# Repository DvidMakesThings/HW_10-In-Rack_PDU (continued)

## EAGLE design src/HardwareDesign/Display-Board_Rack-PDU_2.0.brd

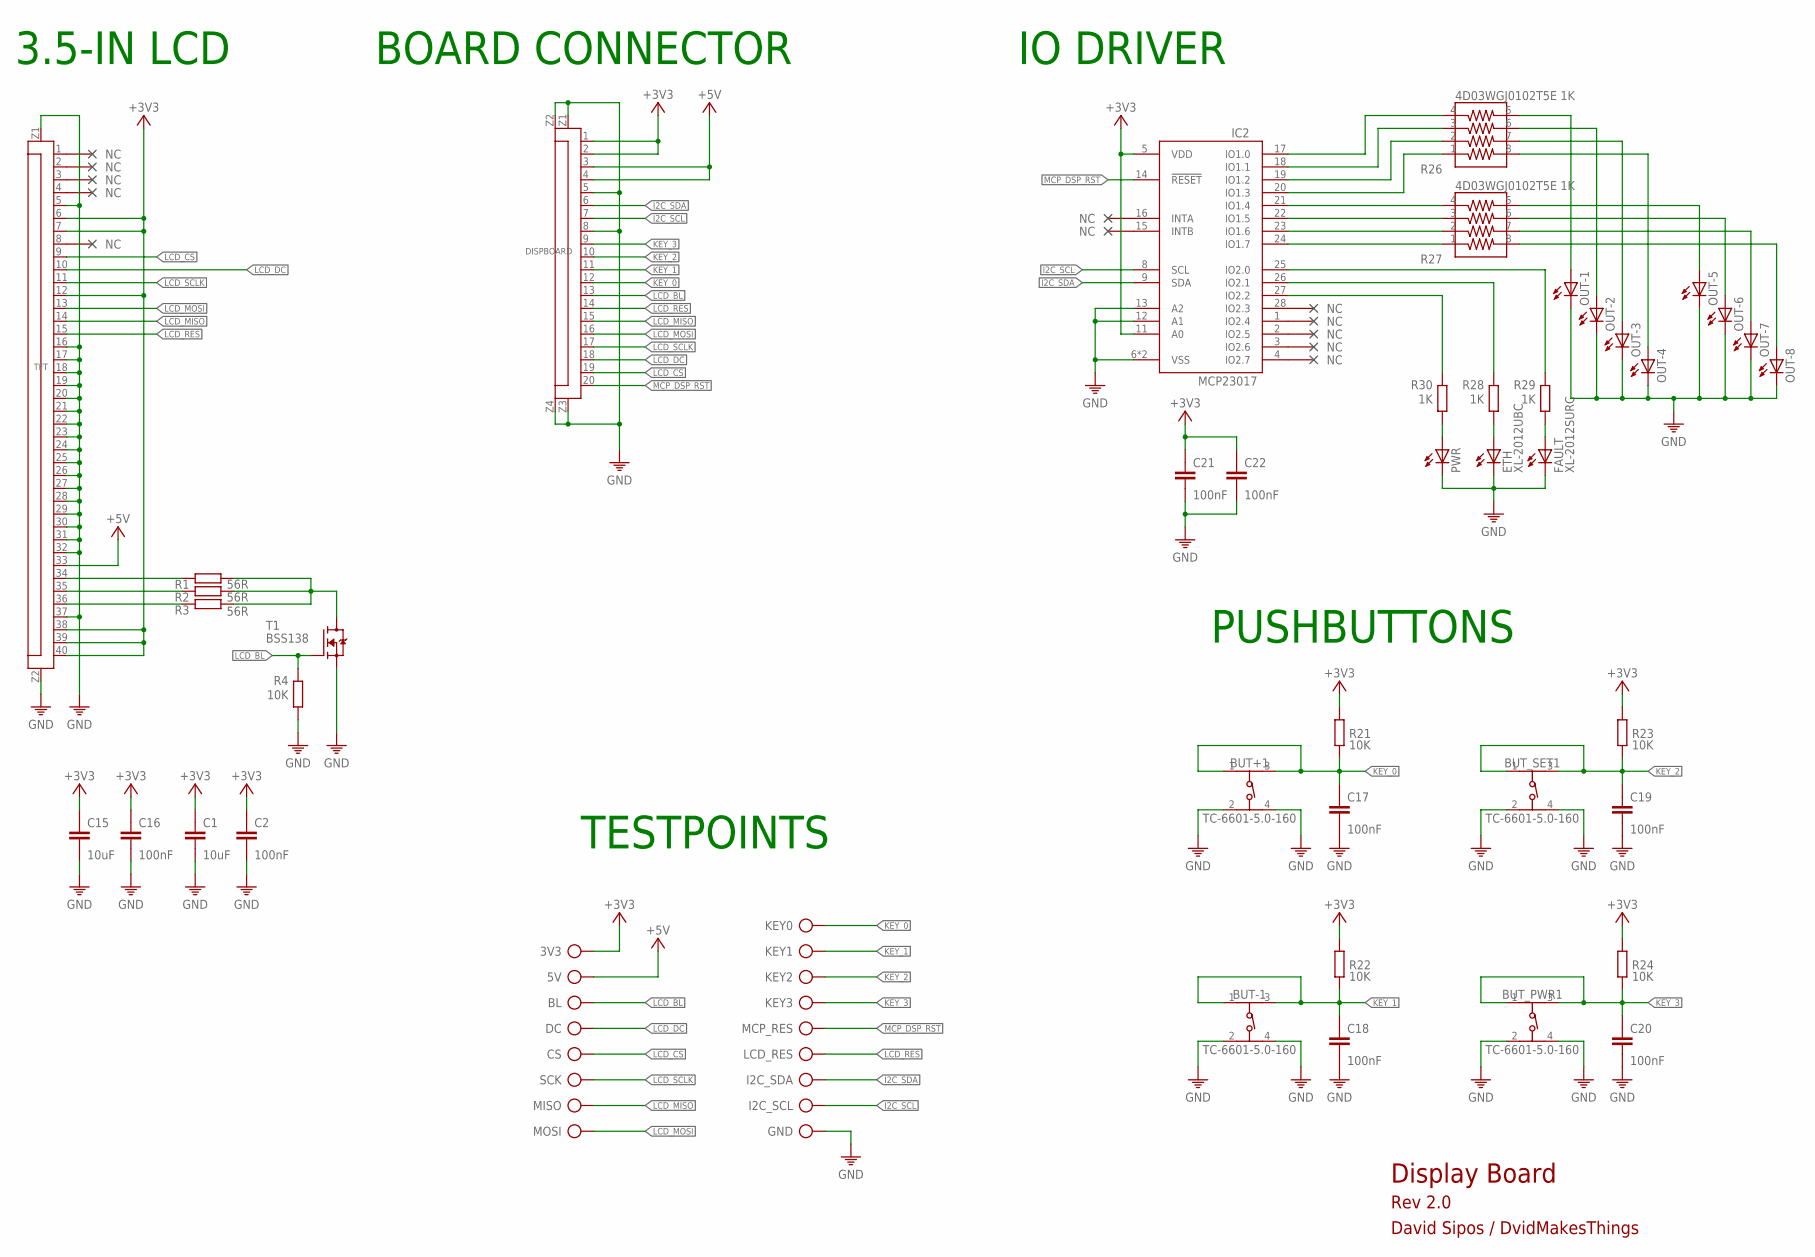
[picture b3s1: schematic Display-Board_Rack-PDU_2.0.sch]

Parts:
3V3, 5V: TP
BL: TP
BUT+1: TC-6601-5.0-160; 430182043816
BUT-1: TC-6601-5.0-160; 430182043816
BUT_PWR1: TC-6601-5.0-160; 430182043816
BUT_SET1: TC-6601-5.0-160; 430182043816
C1, C15: 10uF; C0402
C2, C16, C17, C18, C19, C20, C21, C22: 100nF; C0402
CS: TP
DC: TP
DISPBOARD: FPC20-H; FPC20
ETH: XL-2012UBC; CHIP-LED0805
FAULT: XL-2012SURC; CHIP-LED0805
GND: TP
I2C_SCL, I2C_SDA: TP
IC2: MCP23017-E/ML; QFN28[6X6]ML
KEY0, KEY1, KEY2, KEY3: TP
LCD_RES: TP
MCP_RES: TP
MISO: TP
MOSI: TP
OUT-1, OUT-2, OUT-3, OUT-4, OUT-5, OUT-6, OUT-7, OUT-8: LEDCHIP-LED0805; CHIP-LED0805
PWR: LEDCHIP-LED0805; CHIP-LED0805
R1, R2, R3: 56R; 0402
R4, R21, R22, R23, R24: 10K; 0402
R26, R27: 4D03WGJ0102T5E 1K; 742C083103JP
R28, R29, R30: 1K; 0402
SCK: TP
T1: BSS138; SOT23
TFT: FPC40-HD; FPC40_3.5TFT

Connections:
+3V3: 3V3.TP, C1.1, C2.1, C15.1, C16.1, C21.1, C22.1, DISPBOARD.1, DISPBOARD.2, IC2.5 (VDD), IC2.11 (A0), R21.1, R22.1, R23.1, R24.1, TFT.6, TFT.7, TFT.12, TFT.38, TFT.39, TFT.40
+5V: 5V.TP, DISPBOARD.3, DISPBOARD.4, TFT.33
GND: BUT+1.2, BUT+1.4, BUT-1.2, BUT-1.4, BUT_PWR1.2, BUT_PWR1.4, BUT_SET1.2, BUT_SET1.4, C1.2, C2.2, C15.2, C16.2, C17.2, C18.2, C19.2, C20.2, C21.2, C22.2, DISPBOARD.5, DISPBOARD.8, DISPBOARD.Z1, DISPBOARD.Z2, DISPBOARD.Z3, DISPBOARD.Z4, ETH.C, FAULT.C, GND.TP, IC2.6 (VSS), IC2.12 (A1), IC2.13 (A2), IC2.PAD (VSS), OUT-1.C, OUT-2.C, OUT-3.C, OUT-4.C, OUT-5.C, OUT-6.C, OUT-7.C, OUT-8.C, PWR.C, R4.2, T1.2 (S), TFT.5, TFT.16, TFT.17, TFT.18, TFT.19, TFT.20, TFT.21, TFT.22, TFT.23, TFT.24, TFT.25, TFT.26, TFT.27, TFT.28, TFT.29, TFT.30, TFT.31, TFT.32, TFT.37, TFT.Z1, TFT.Z2
I2C_SCL: DISPBOARD.7, I2C_SCL.TP, IC2.8 (SCL)
I2C_SDA: DISPBOARD.6, I2C_SDA.TP, IC2.9 (SDA)
KEY_0: BUT+1.1, BUT+1.3, C17.1, DISPBOARD.12, KEY0.TP, R21.2
KEY_1: BUT-1.1, BUT-1.3, C18.1, DISPBOARD.11, KEY1.TP, R22.2
KEY_2: BUT_SET1.1, BUT_SET1.3, C19.1, DISPBOARD.10, KEY2.TP, R23.2
KEY_3: BUT_PWR1.1, BUT_PWR1.3, C20.1, DISPBOARD.9, KEY3.TP, R24.2
LCD_BL: BL.TP, DISPBOARD.13, R4.1, T1.1 (G)
LCD_CS: CS.TP, DISPBOARD.19, TFT.9
LCD_DC: DC.TP, DISPBOARD.18, TFT.10
LCD_MISO: DISPBOARD.15, MISO.TP, TFT.14
LCD_MOSI: DISPBOARD.16, MOSI.TP, TFT.13
LCD_RES: DISPBOARD.14, LCD_RES.TP, TFT.15
LCD_SCLK: DISPBOARD.17, SCK.TP, TFT.11
MCP_DSP_RST: DISPBOARD.20, IC2.14 (!RESET), MCP_RES.TP
unnamed: R2.2, TFT.35
unnamed: R3.2, TFT.36
unnamed: R1.1, R2.1, R3.1, T1.3 (D)
unnamed: R1.2, TFT.34
unnamed: IC2.26 (IO2.1), R28.1
unnamed: IC2.27 (IO2.2), R30.1
unnamed: IC2.25 (IO2.0), R29.1
unnamed: IC2.17 (IO1.0), R26.4
unnamed: IC2.18 (IO1.1), R26.3
unnamed: IC2.19 (IO1.2), R26.2
unnamed: IC2.20 (IO1.3), R26.1
unnamed: IC2.21 (IO1.4), R27.4
unnamed: IC2.22 (IO1.5), R27.3
unnamed: IC2.23 (IO1.6), R27.2
unnamed: IC2.24 (IO1.7), R27.1
unnamed: OUT-1.A, R26.5
unnamed: OUT-2.A, R26.6
unnamed: OUT-3.A, R26.7
unnamed: OUT-4.A, R26.8
unnamed: OUT-5.A, R27.5
unnamed: OUT-6.A, R27.6
unnamed: OUT-7.A, R27.7
unnamed: OUT-8.A, R27.8
unnamed: FAULT.A, R29.2
unnamed: ETH.A, R28.2
unnamed: PWR.A, R30.2

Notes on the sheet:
BOARD CONNECTOR
3.5-IN LCD
PUSHBUTTONS
IO DRIVER
Display Board
Rev 2.0
David Sipos / DvidMakesThings
TESTPOINTS

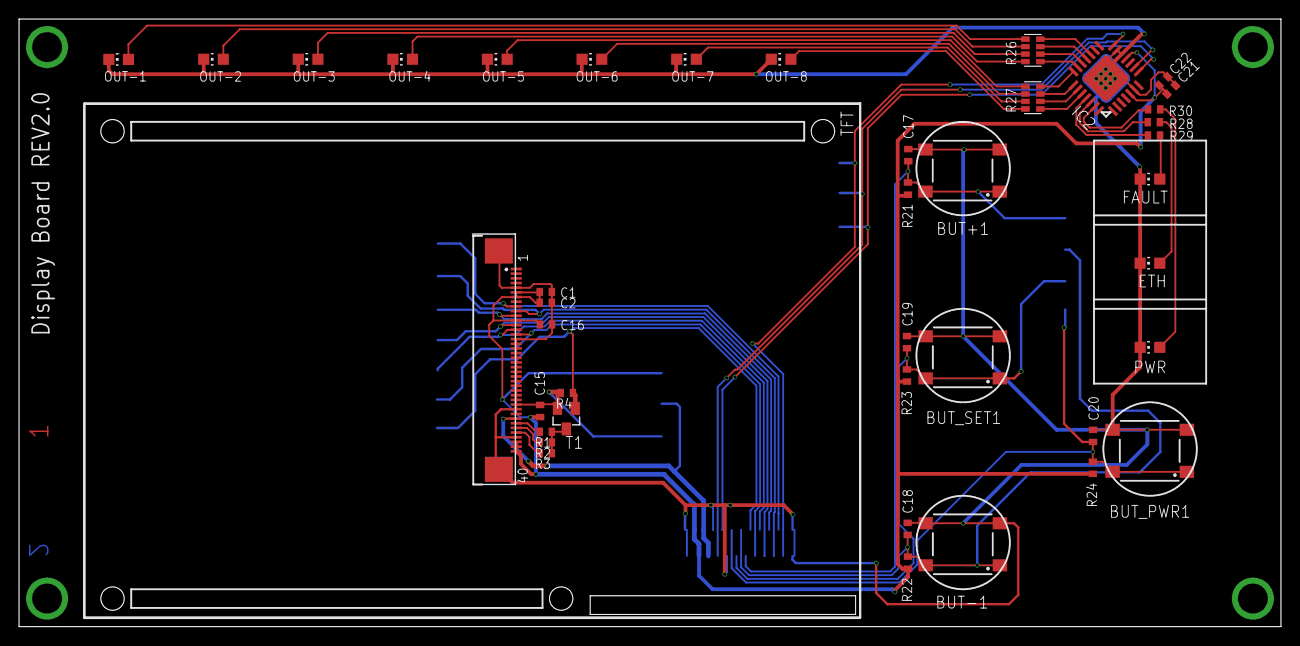
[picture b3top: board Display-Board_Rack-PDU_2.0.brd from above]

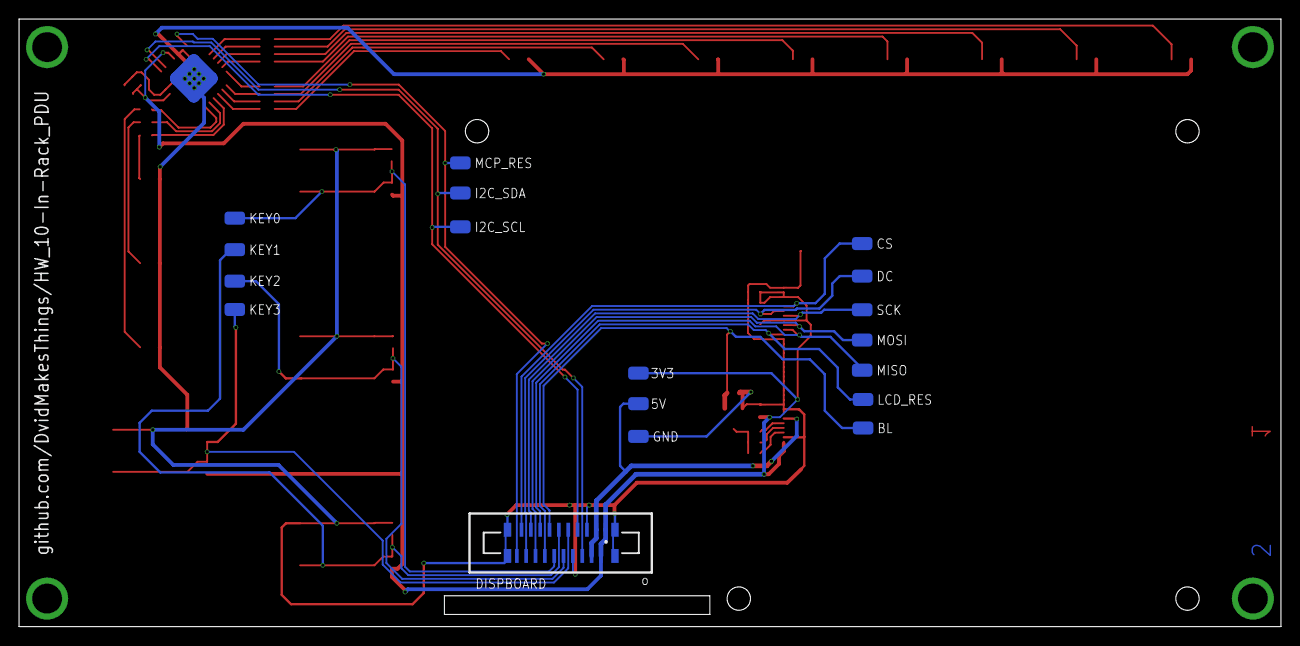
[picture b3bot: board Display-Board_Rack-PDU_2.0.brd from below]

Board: 2 copper layers, 135.0 x 65.0 mm, 60 parts (18 on the bottom side), 43 nets.

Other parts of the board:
U$1: 2-LAYER

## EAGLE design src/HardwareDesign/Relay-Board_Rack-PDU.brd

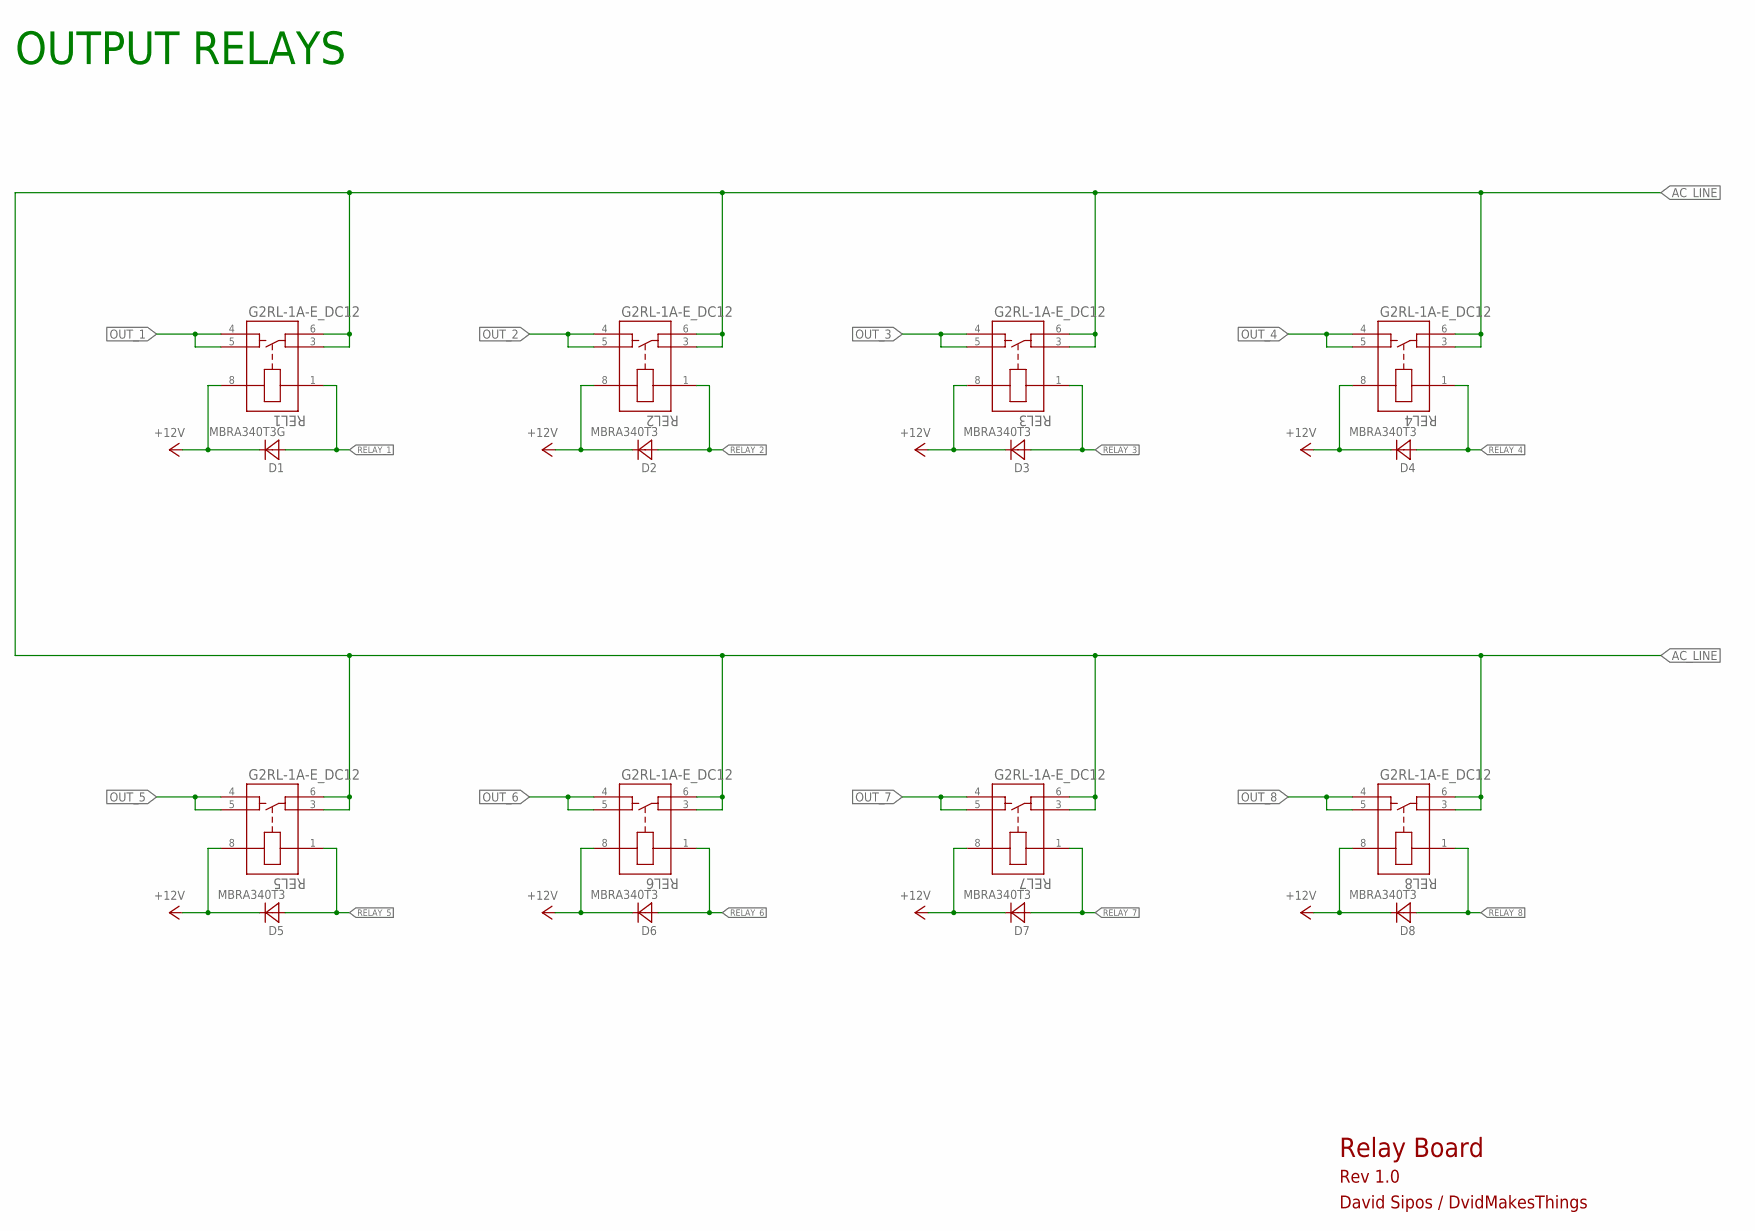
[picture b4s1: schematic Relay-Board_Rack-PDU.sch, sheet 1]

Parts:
D1: MBRA340T3G; SMA
D2, D3, D4, D5, D6, D7, D8: MBRA340T3; SMA
REL1, REL2, REL3, REL4, REL5, REL6, REL7, REL8: G2RL-1A-E_DC12; RELAY_G2RL-1A-E_DC5_OMR

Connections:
+12V: D1.C, D2.C, D3.C, D4.C, D5.C, D6.C, D7.C, D8.C, REL1.8, REL2.8, REL3.8, REL4.8, REL5.8, REL6.8, REL7.8, REL8.8; also elsewhere on the board
AC_LINE: REL1.3, REL1.6, REL2.3, REL2.6, REL3.3, REL3.6, REL4.3, REL4.6, REL5.3, REL5.6, REL6.3, REL6.6, REL7.3, REL7.6, REL8.3, REL8.6; also elsewhere on the board
OUT_1: REL1.4, REL1.5
OUT_2: REL2.4, REL2.5
OUT_3: REL3.4, REL3.5
OUT_4: REL4.4, REL4.5
OUT_5: REL5.4, REL5.5
OUT_6: REL6.4, REL6.5
OUT_7: REL7.4, REL7.5
OUT_8: REL8.4, REL8.5
RELAY_1: D1.A, REL1.1; also elsewhere on the board
RELAY_2: D2.A, REL2.1; also elsewhere on the board
RELAY_3: D3.A, REL3.1; also elsewhere on the board
RELAY_4: D4.A, REL4.1; also elsewhere on the board
RELAY_5: D5.A, REL5.1; also elsewhere on the board
RELAY_6: D6.A, REL6.1; also elsewhere on the board
RELAY_7: D7.A, REL7.1; also elsewhere on the board
RELAY_8: D8.A, REL8.1; also elsewhere on the board

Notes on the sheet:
OUTPUT RELAYS
Relay Board
Rev 1.0
David Sipos / DvidMakesThings

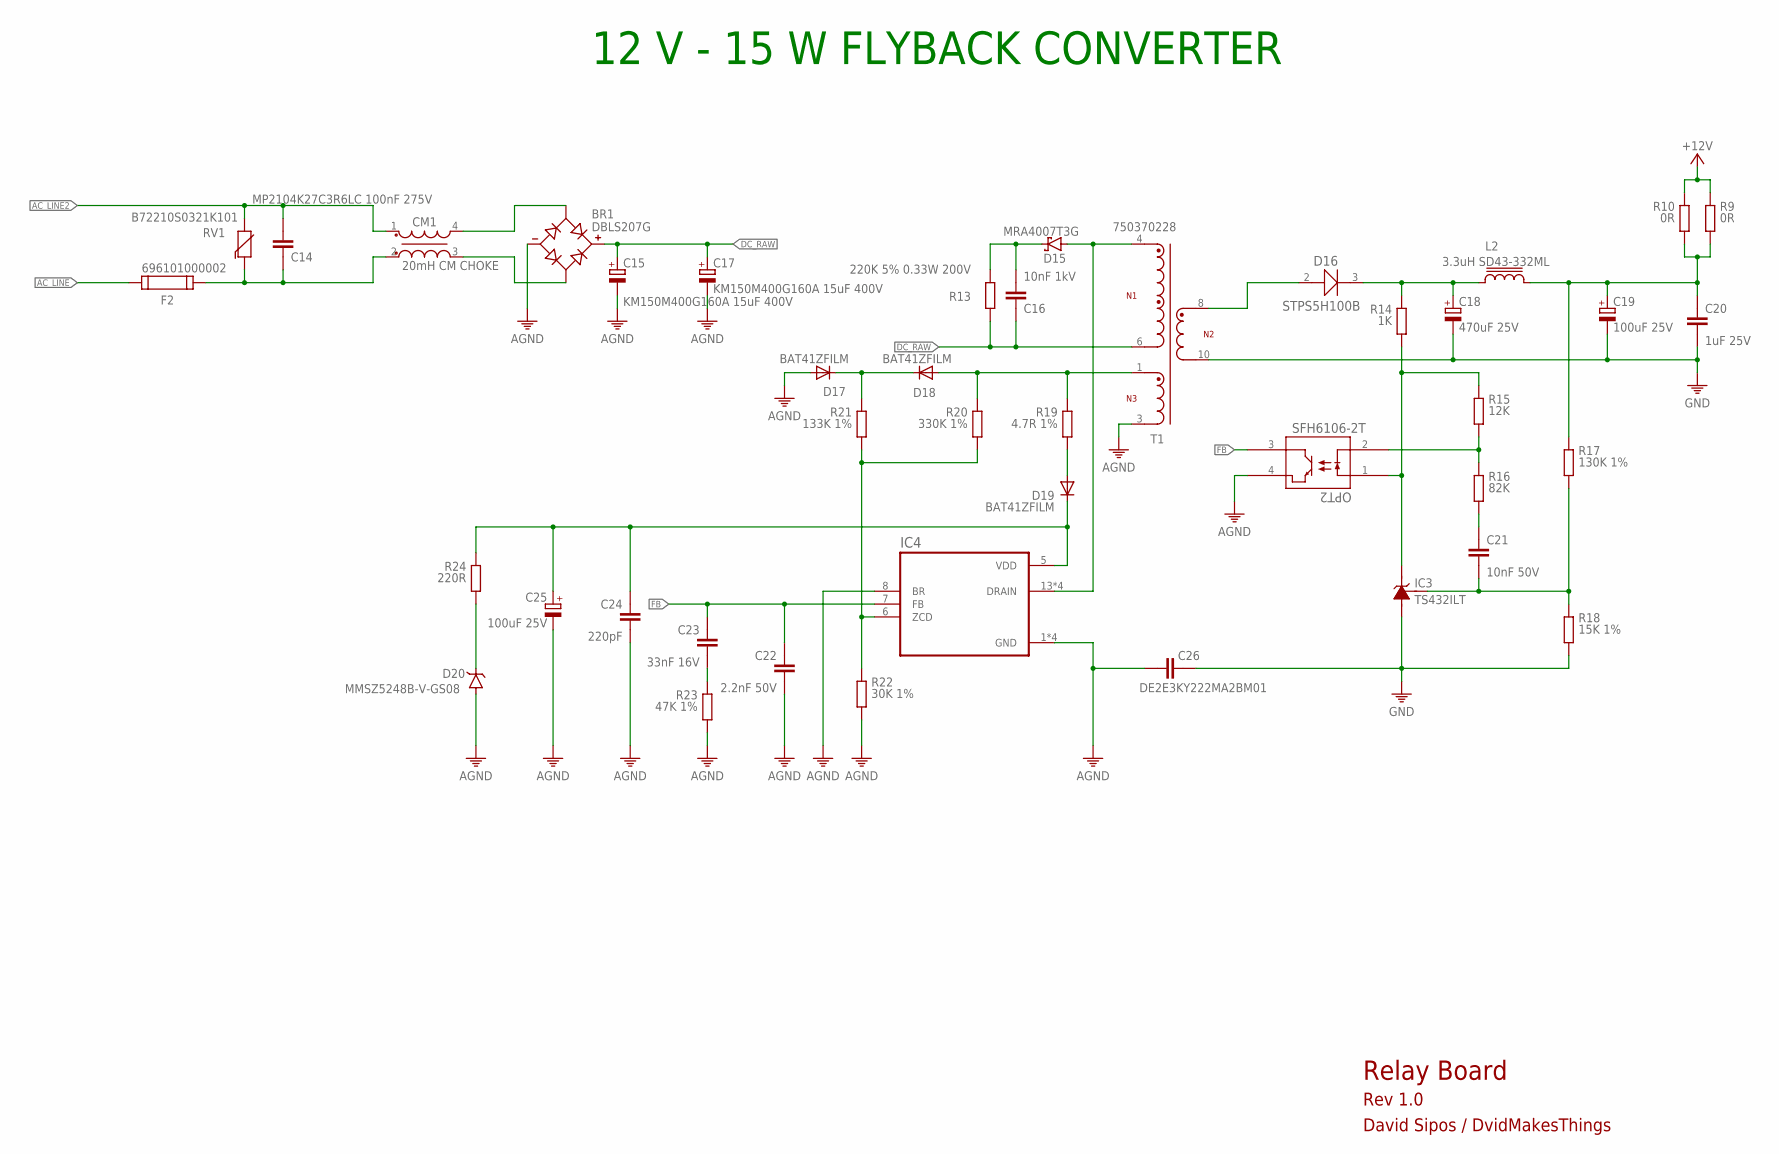
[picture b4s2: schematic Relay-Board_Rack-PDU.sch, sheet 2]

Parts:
BR1: DBLS207G; DIOB_DBLS207G
C14: MP2104K27C3R6LC 100nF 275V; 103-275V
C15, C17: KM150M400G160A 15uF 400V; CAPPRD550W110D1250H2500B
C16: 10nF 1kV; C1206
C18: 470uF 25V; CAPPRD508W65D1000H1100B
C19, C25: 100uF 25V; CAPPRD508W65D1000H1100B
C20: 1uF 25V; C0805
C21: 10nF 50V; C0805
C22: 2.2nF 50V; C0603
C23: 33nF 16V; C0603
C24: 220pF; C0805
C26: DE2E3KY222MA2BM01; AR21AC103K4R
CM1: 20mH CM CHOKE; WE-CMB_XS_744821120
D15: MRA4007T3G; SMA
D16: STPS5H100B; DPAK_STM
D17, D18, D19: BAT41ZFILM; SOD-123_MINI-SMA
D20: MMSZ5248B-V-GS08; DO214AC
F2: 696101000002
IC3: TS432ILT; SOT23
IC4: VIPER35HD
L2: 3.3uH SD43-332ML; INDUCTOR-BOURNS_SRN8040
OPT2: SFH6106-2T; SMD-4_SFH610X_VIS-M
R9, R10: 0R; 0805
R13: 220K 5% 0.33W 200V; 1206
R14: 1K; 0603
R15: 12K; 0603
R16: 82K; 0603
R17: 130K 1%; 0603
R18: 15K 1%; 0603
R19: 4.7R 1%; 0603
R20: 330K 1%; 0603
R21: 133K 1%; 0603
R22: 30K 1%; 0603
R23: 47K 1%; 0603
R24: 220R; 0805
RV1: B72210S0321K101; WE-VD_10MM_820412001
T1: 750370228; WE-OLSTM_EE20_L22.2W25H16

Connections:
+12V: R9.1, R10.1; also elsewhere on the board
AC_LINE: F2.1; also elsewhere on the board
AC_LINE2: C14.2, CM1.1, RV1.2
AGND: BR1.-, C15.2 (-), C17.2 (-), C22.2, C24.2, C25.2 (-), C26.1, D17.A, D20.A, IC4.1 (GND), IC4.2 (GND), IC4.3 (GND), IC4.4 (GND), IC4.8 (BR), OPT2.4, R22.2, R23.2, T1.3
DC_RAW: BR1.+, C15.1 (+), C16.1, C17.1 (+), R13.2, T1.6
FB: C22.1, C23.1, IC4.7 (FB), OPT2.3
GND: C18.2 (-), C19.2 (-), C20.2, C26.2, IC3.3, R18.2, T1.10; also elsewhere on the board
unnamed: C19.1 (+), C20.1, L2.2, R9.2, R10.2, R17.1
unnamed: BR1.AC1, CM1.4
unnamed: BR1.AC2, CM1.3
unnamed: C14.1, CM1.2, F2.2, RV1.1
unnamed: C16.2, D15.C, R13.1
unnamed: D15.A, IC4.13 (DRAIN), IC4.14 (DRAIN), IC4.15 (DRAIN), IC4.16 (DRAIN), T1.4
unnamed: D16.2, T1.8
unnamed: C18.1 (+), D16.3, L2.1, R14.1
unnamed: IC3.2, OPT2.1, R14.2, R15.1
unnamed: OPT2.2, R15.2, R16.1
unnamed: C21.1, R16.2
unnamed: C21.2, IC3.1, R17.2, R18.1
unnamed: C24.1, C25.1 (+), D19.C, IC4.5 (VDD), R24.1
unnamed: D19.A, R19.2
unnamed: D18.A, R19.1, R20.1, T1.1
unnamed: D17.C, D18.C, R21.1
unnamed: IC4.6 (ZCD), R20.2, R21.2, R22.1
unnamed: C23.2, R23.1
unnamed: D20.C, R24.2

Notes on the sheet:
12 V - 15 W FLYBACK CONVERTER
Relay Board
Rev 1.0
David Sipos / DvidMakesThings

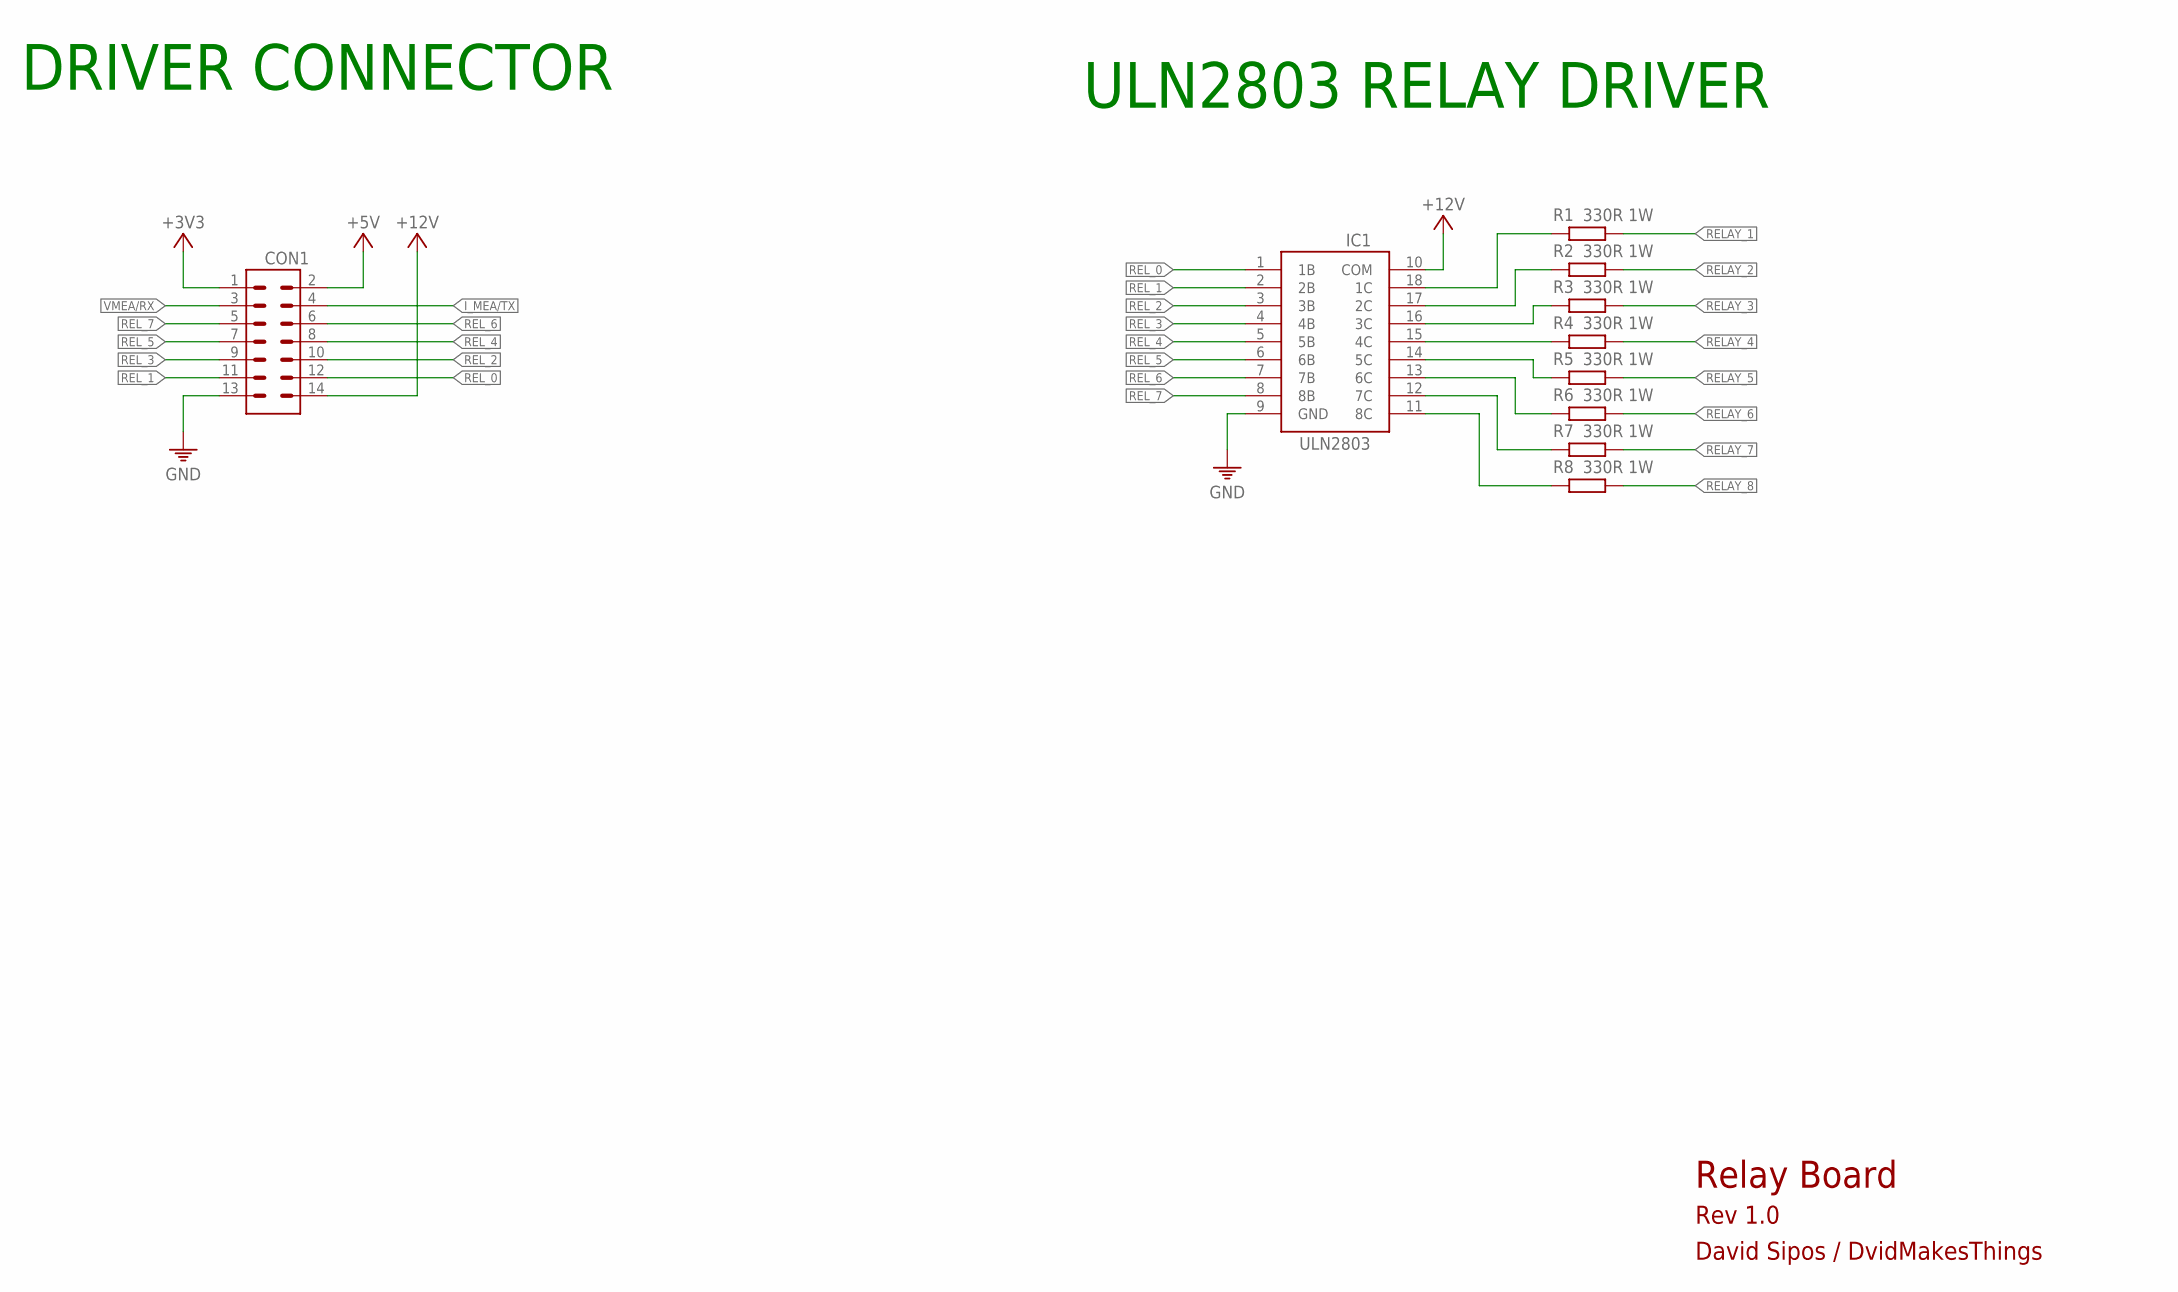
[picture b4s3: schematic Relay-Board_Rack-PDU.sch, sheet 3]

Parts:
CON1: CON-2X7; 2X7
IC1: ULN2803A; SO18
R1, R2, R3, R4, R5, R6, R7, R8: 330R 1W; 1206

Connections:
+3V3: CON1.1
+5V: CON1.2
+12V: CON1.14, IC1.10 (COM); also elsewhere on the board
GND: CON1.13, IC1.9 (GND); also elsewhere on the board
I_MEA/TX: CON1.4
unnamed: IC1.18 (1C), R1.1
unnamed: IC1.17 (2C), R2.1
unnamed: IC1.16 (3C), R3.1
unnamed: IC1.15 (4C), R4.1
unnamed: IC1.14 (5C), R5.1
unnamed: IC1.13 (6C), R6.1
unnamed: IC1.12 (7C), R7.1
unnamed: IC1.11 (8C), R8.1
RELAY_1: R1.2; also elsewhere on the board
RELAY_2: R2.2; also elsewhere on the board
RELAY_3: R3.2; also elsewhere on the board
RELAY_4: R4.2; also elsewhere on the board
RELAY_5: R5.2; also elsewhere on the board
RELAY_6: R6.2; also elsewhere on the board
RELAY_7: R7.2; also elsewhere on the board
RELAY_8: R8.2; also elsewhere on the board
REL_0: CON1.12, IC1.1 (1B)
REL_1: CON1.11, IC1.2 (2B)
REL_2: CON1.10, IC1.3 (3B)
REL_3: CON1.9, IC1.4 (4B)
REL_4: CON1.8, IC1.5 (5B)
REL_5: CON1.7, IC1.6 (6B)
REL_6: CON1.6, IC1.7 (7B)
REL_7: CON1.5, IC1.8 (8B)
VMEA/RX: CON1.3

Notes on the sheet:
Relay Board
Rev 1.0
David Sipos / DvidMakesThings
DRIVER CONNECTOR
ULN2803 RELAY DRIVER

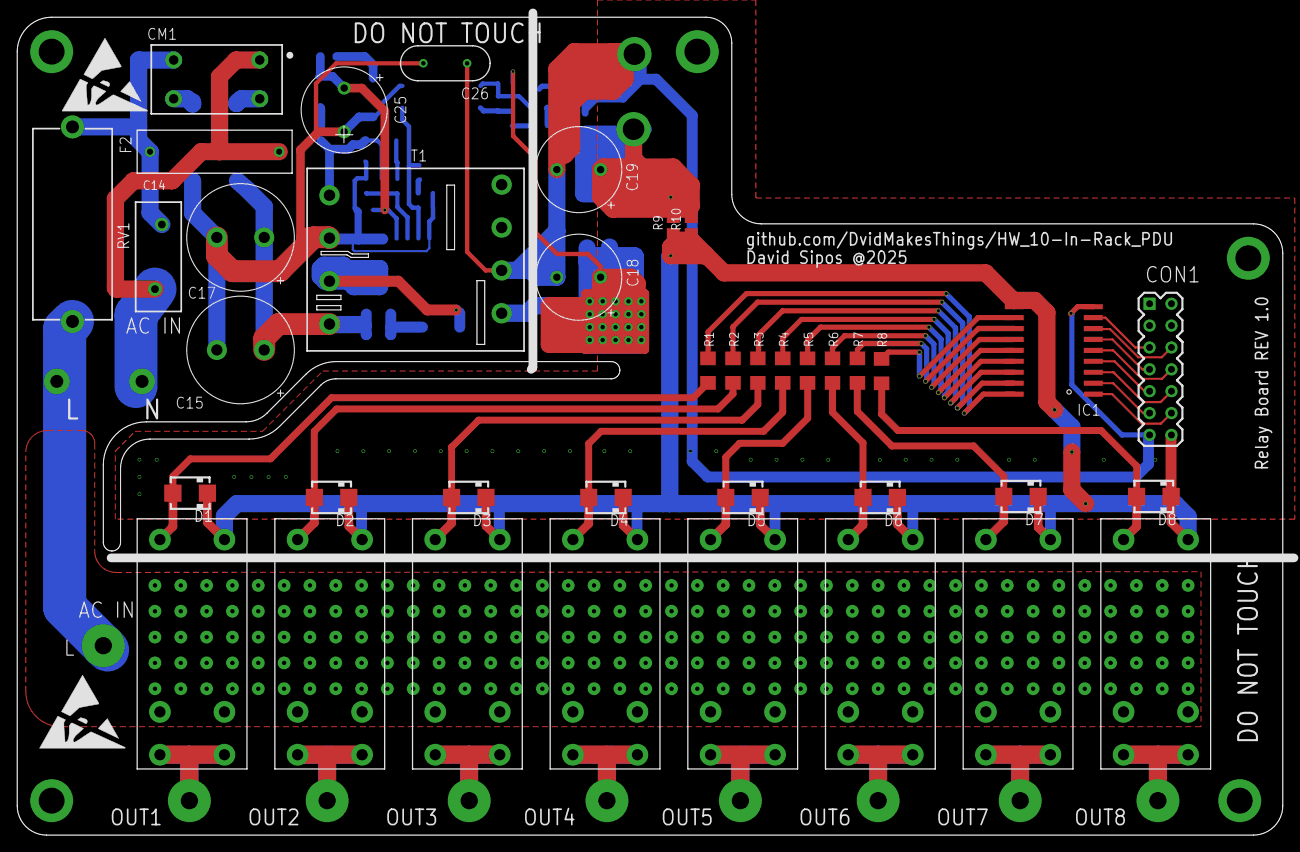
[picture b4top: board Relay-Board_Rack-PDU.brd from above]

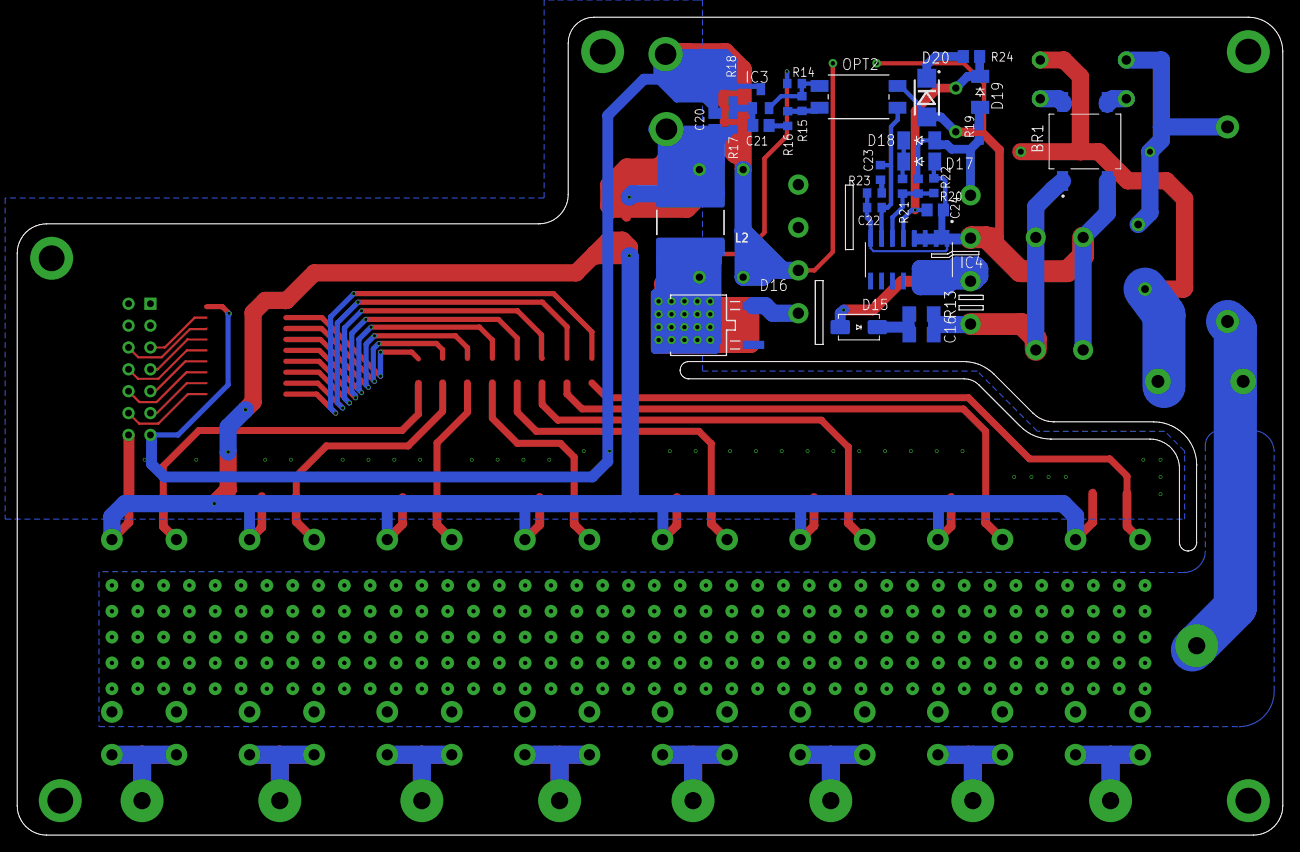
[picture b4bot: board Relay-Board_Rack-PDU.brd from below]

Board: 2 copper layers, 147.0 x 95.0 mm, 70 parts (29 on the bottom side), 58 nets.

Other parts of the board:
U$1, U$2: ESD_10.00

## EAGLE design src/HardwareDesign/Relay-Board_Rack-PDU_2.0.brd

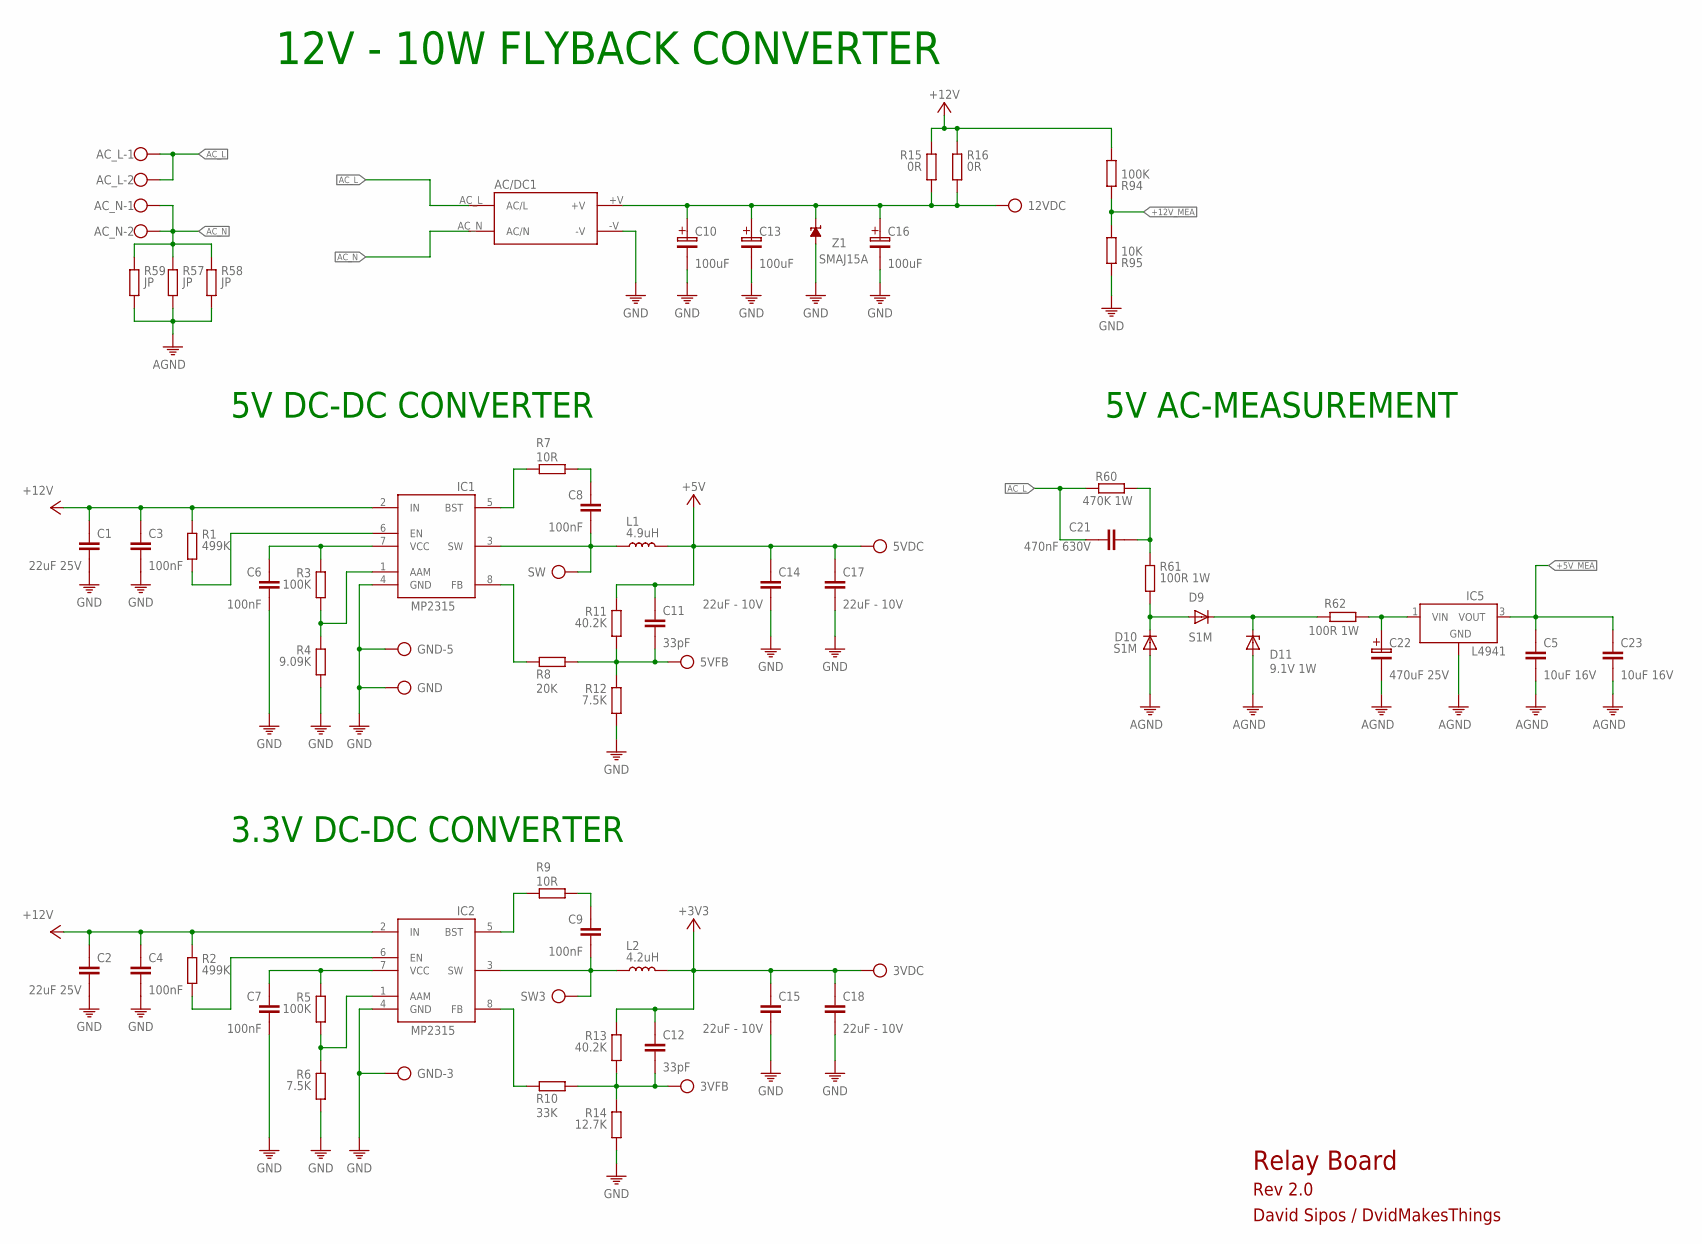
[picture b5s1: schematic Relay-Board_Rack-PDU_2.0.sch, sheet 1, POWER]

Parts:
3VDC, 3VFB, 5VDC, 5VFB, 12VDC: TP
AC/DC1: IRM_10_12
AC_L: W237-102
AC_N: W237-102
C1, C2: 22uF 25V; C1206
C3, C4, C6, C7, C8, C9: 100nF; 0402
C5, C23: 10uF 16V; C1206
C10, C13, C16: 100uF; 100UF-16V
C11, C12: 33pF; 0402
C14, C15, C17, C18: 22uF - 10V; C1206
C21: 470nF 630V; 2225
C22: 470uF 25V; 100UF-16V
D9, D10: S1M; SMA
D11: 9.1V 1W; SMB
GND: TP
GND-3, GND-5: TP
IC1: MP2315GJ-Z; SOT65P280X110-8N
IC2: MP2315S; SOT65P280X110-8N
IC5: BA50BC0FP-E2; DPAK
L1: 4.9uH; SRR5228A
L2: 4.2uH; SRR5228A
R1, R2: 499K; 0402
R3, R5, R94: 100K; 0402
R4: 9.09K; 0402
R6, R12: 7.5K; 0402
R7, R9: 10R; 0402
R8: 20K; 0402
R10: 33K; 0402
R11, R13: 40.2K; 0402
R14: 12.7K; 0402
R15, R16: 0R; 0805
R57, R58, R59: JP; 0402
R60: 470K 1W; 2512
R61, R62: 100R 1W; 2512
R95: 10K; 0402
SW, SW3: TP
Z1: SMAJ15A; SUPRESSOR_SMAJ

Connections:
5VFB: 5VFB.TP, C11.2, R8.2, R11.2, R12.1
+3V3: 3VDC.TP, C12.1, C15.1, C18.1, L2.2, R13.1; also elsewhere on the board
+5V: 5VDC.TP, C11.1, C14.1, C17.1, L1.2, R11.1; also elsewhere on the board
+5V_MEA: C5.1, C23.1, IC5.3 (VOUT); also elsewhere on the board
+12V: C1.1, C2.1, C3.1, C4.1, IC1.2 (IN), IC2.2 (IN), R1.1, R2.1, R15.1, R16.1, R94.2; also elsewhere on the board
+12V_MEA: R94.1, R95.2; also elsewhere on the board
AC_L: AC/DC1.AC_L (AC/L), AC_L.1, AC_L.2, C21.1, R60.1; also elsewhere on the board
AC_N: AC/DC1.AC_N (AC/N), AC_N.1, AC_N.2, R57.1, R58.1, R59.1
AGND: C5.2, C22.2, C23.2, D10.A, D11.A, IC5.4 (GND), R57.2, R58.2, R59.2; also elsewhere on the board
GND: AC/DC1.-V, C1.2, C2.2, C3.2, C4.2, C6.2, C7.2, C10.2, C13.2, C14.2, C15.2, C16.2, C17.2, C18.2, GND.TP, GND-3.TP, GND-5.TP, IC1.4 (GND), IC2.4 (GND), R4.2, R6.2, R12.2, R14.2, R95.1, Z1.A; also elsewhere on the board
unnamed: 12VDC.TP, AC/DC1.+V, C10.1, C13.1, C16.1, R15.2, R16.2, Z1.C
unnamed: C21.2, R60.2, R61.1
unnamed: IC1.5 (BST), R7.2
unnamed: IC1.8 (FB), R8.1
unnamed: C8.1, R7.1
unnamed: IC1.6 (EN), R1.2
unnamed: D9.A, D10.C, R61.2
unnamed: C6.1, IC1.7 (VCC), R3.1
unnamed: C22.1, IC5.1 (VIN), R62.2
unnamed: D9.C, D11.C, R62.1
unnamed: IC2.5 (BST), R9.2
unnamed: IC2.8 (FB), R10.1
unnamed: C9.1, R9.1
unnamed: 3VFB.TP, C12.2, R10.2, R13.2, R14.1
unnamed: IC2.6 (EN), R2.2
unnamed: C7.1, IC2.7 (VCC), R5.1
unnamed: IC1.1 (AAM), R3.2, R4.1
unnamed: IC2.1 (AAM), R5.2, R6.1
SW3: C9.2, IC2.3 (SW), L2.1, SW3.TP
SW5: C8.2, IC1.3 (SW), L1.1, SW.TP

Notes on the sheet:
12V - 10W FLYBACK CONVERTER
Relay Board
Rev 2.0
David Sipos / DvidMakesThings
5V DC-DC CONVERTER
3.3V DC-DC CONVERTER
5V AC-MEASUREMENT
